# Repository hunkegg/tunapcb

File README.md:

# tuna pcb
slack username: egg_splats

## description
a new keychain to add to my ever-growing collection mweheheheheh >:3  
  
this is a pcb made for the solder YSWS by Hack Club  
i was craving tuna when i came up with this, thus resulting in the fishy theme of this keychain  
featuring:  
* 2 LEDs with pushy buttons
* vibrating motor
* fish 🐟

## parts list
* 1 battery holder
* 2 220Ω resistors
* 1 4.7Ω resistor
* 3 6mm push buttons
* 1 vibration motor

## schematic

## PCB

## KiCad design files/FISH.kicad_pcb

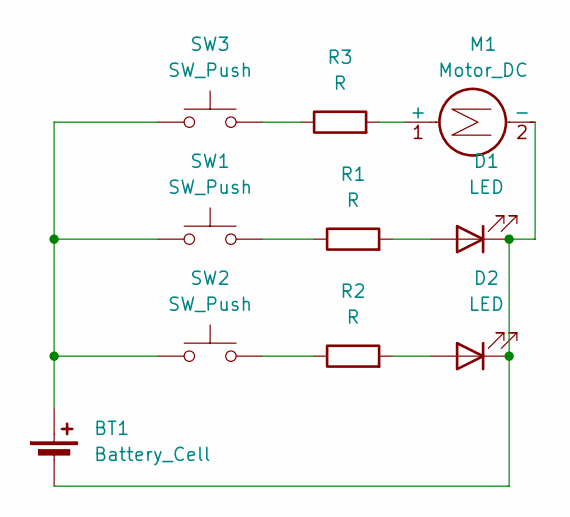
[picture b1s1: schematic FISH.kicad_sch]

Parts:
BT1: Battery_Cell; BatteryHolder_Keystone_3034_1x20mm
D1, D2: LED; LED_D5.0mm
M1: Motor_DC; PinHeader_1x02_P2.54mm_Vertical
R1, R2, R3: R; R_Axial_DIN0207_L6.3mm_D2.5mm_P7.62mm_Horizontal
SW1, SW2, SW3: SW_Push; SW_PUSH_6mm

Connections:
unnamed: BT1.1 (+), SW1.1, SW2.1, SW3.1
unnamed: BT1.2 (-), D1.1 (K), D2.1 (K), M1.2 (-)
unnamed: D1.2 (A), R1.2
unnamed: D2.2 (A), R2.2
unnamed: M1.1 (+), R3.2
unnamed: R1.1, SW1.2
unnamed: R2.1, SW2.2
unnamed: R3.1, SW3.2

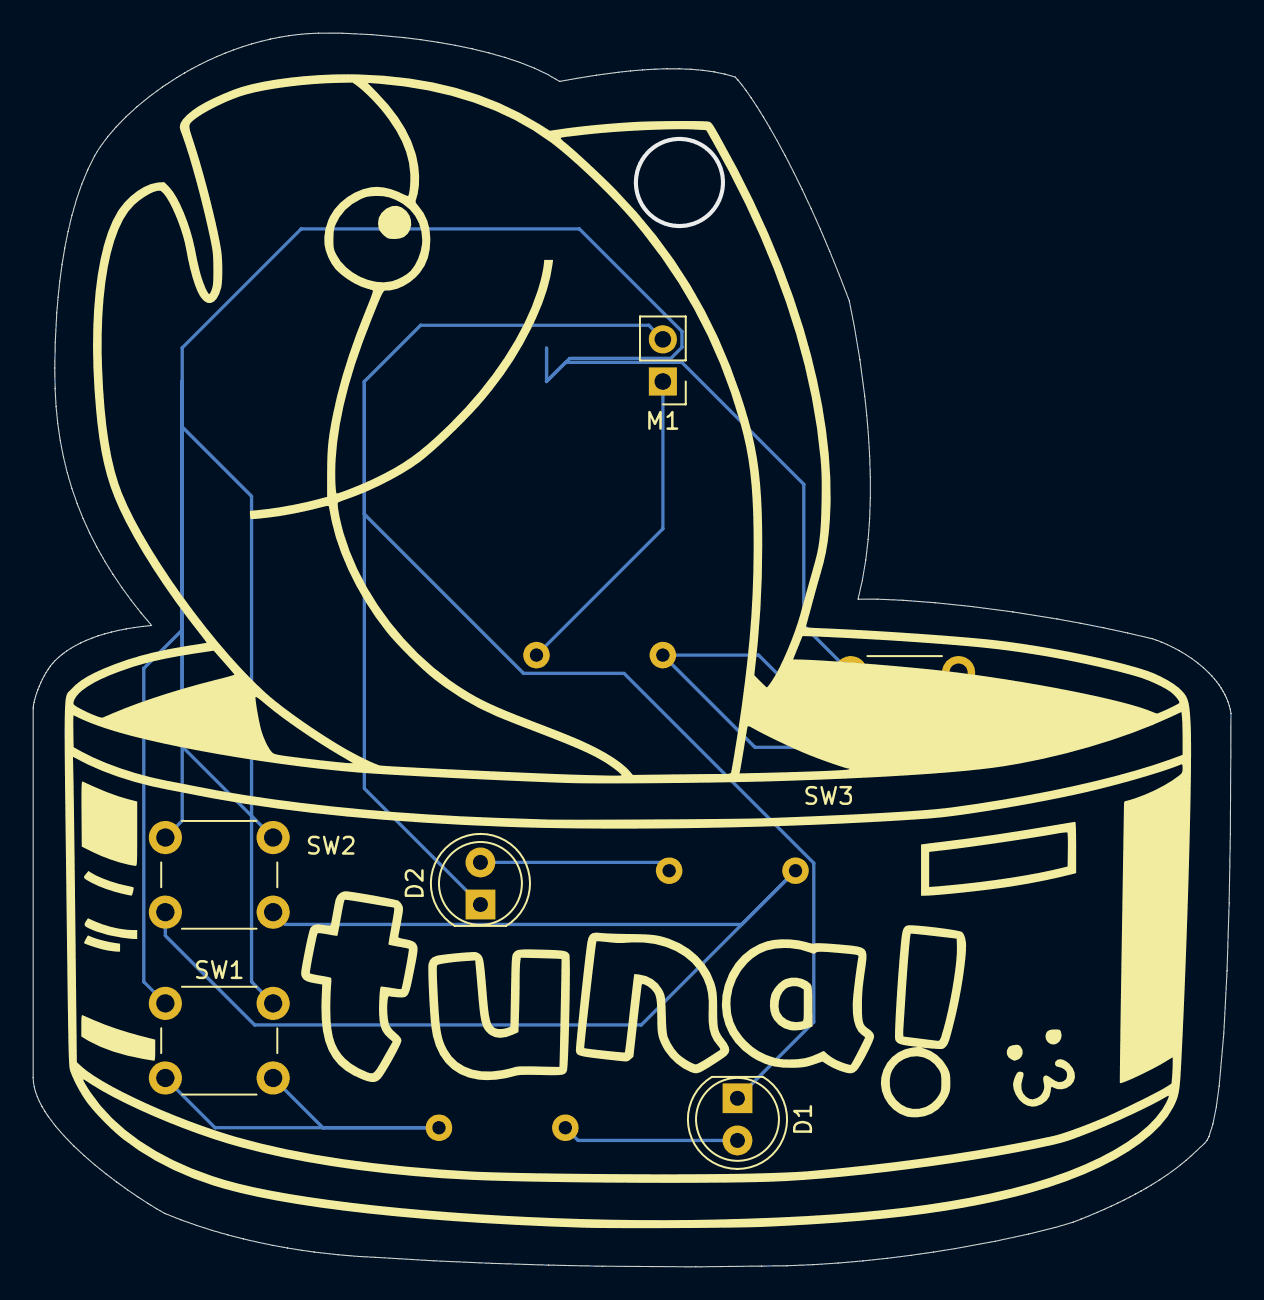
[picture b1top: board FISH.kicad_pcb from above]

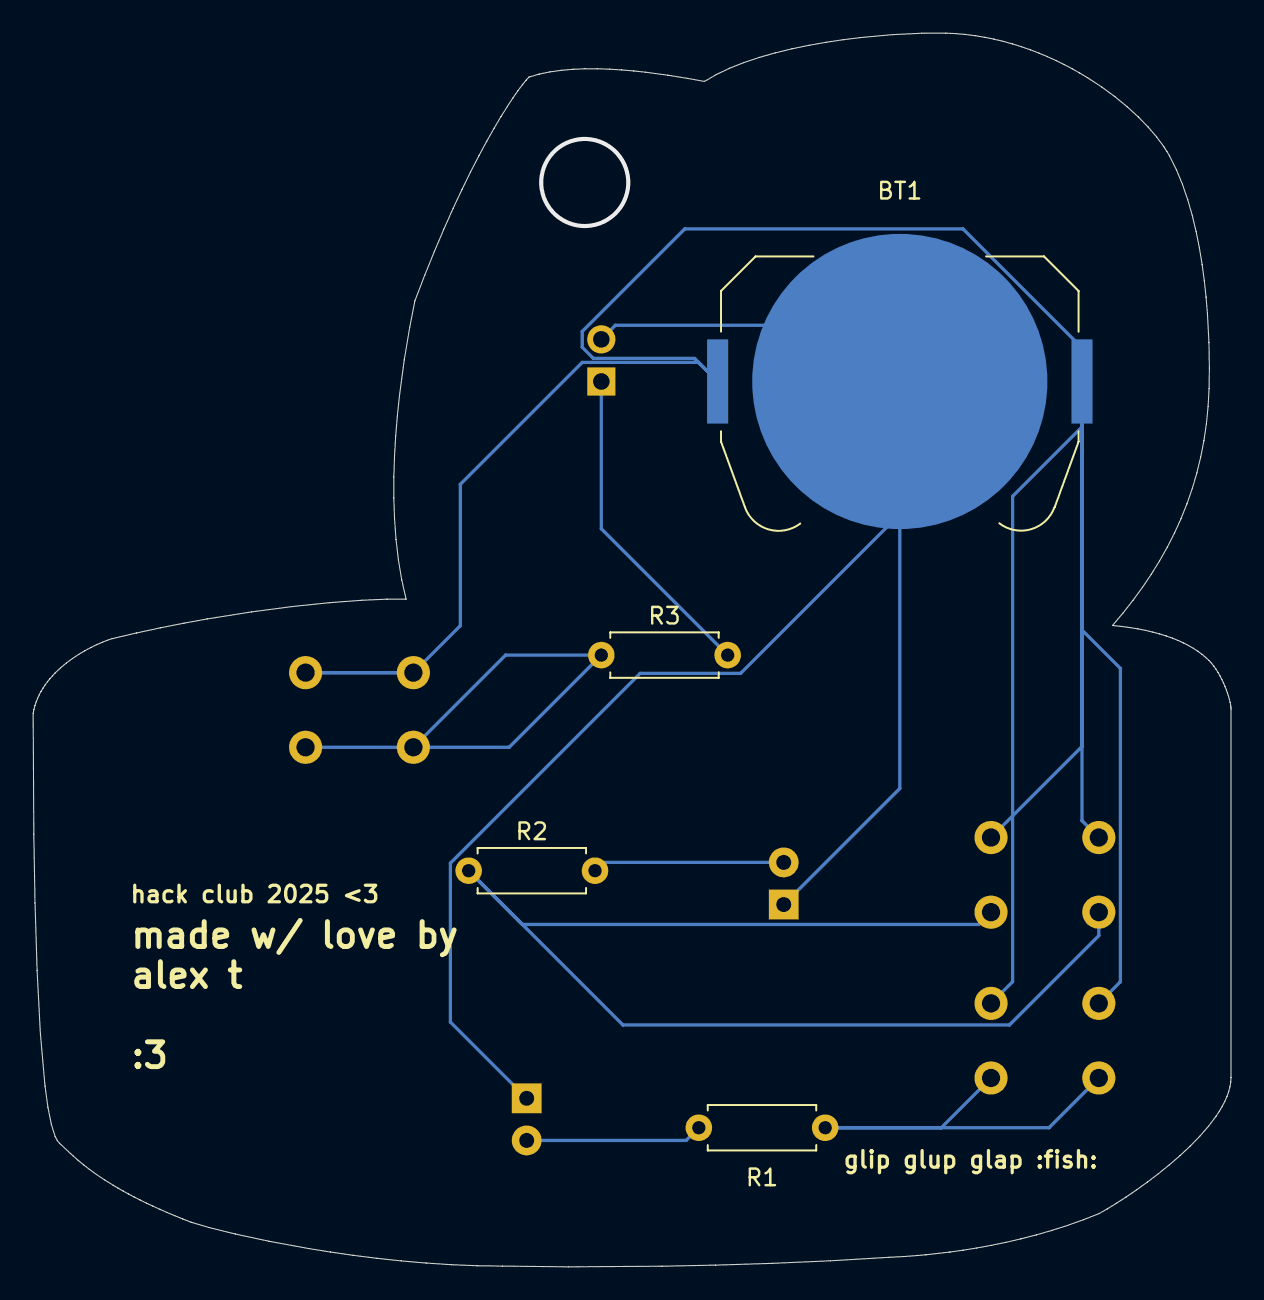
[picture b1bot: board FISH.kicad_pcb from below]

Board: 2 copper layers, 72.2 x 74.4 mm, 11 parts (4 on the bottom side), 8 nets.

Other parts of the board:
G: LOGO

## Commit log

2025-04-26 Create blah
